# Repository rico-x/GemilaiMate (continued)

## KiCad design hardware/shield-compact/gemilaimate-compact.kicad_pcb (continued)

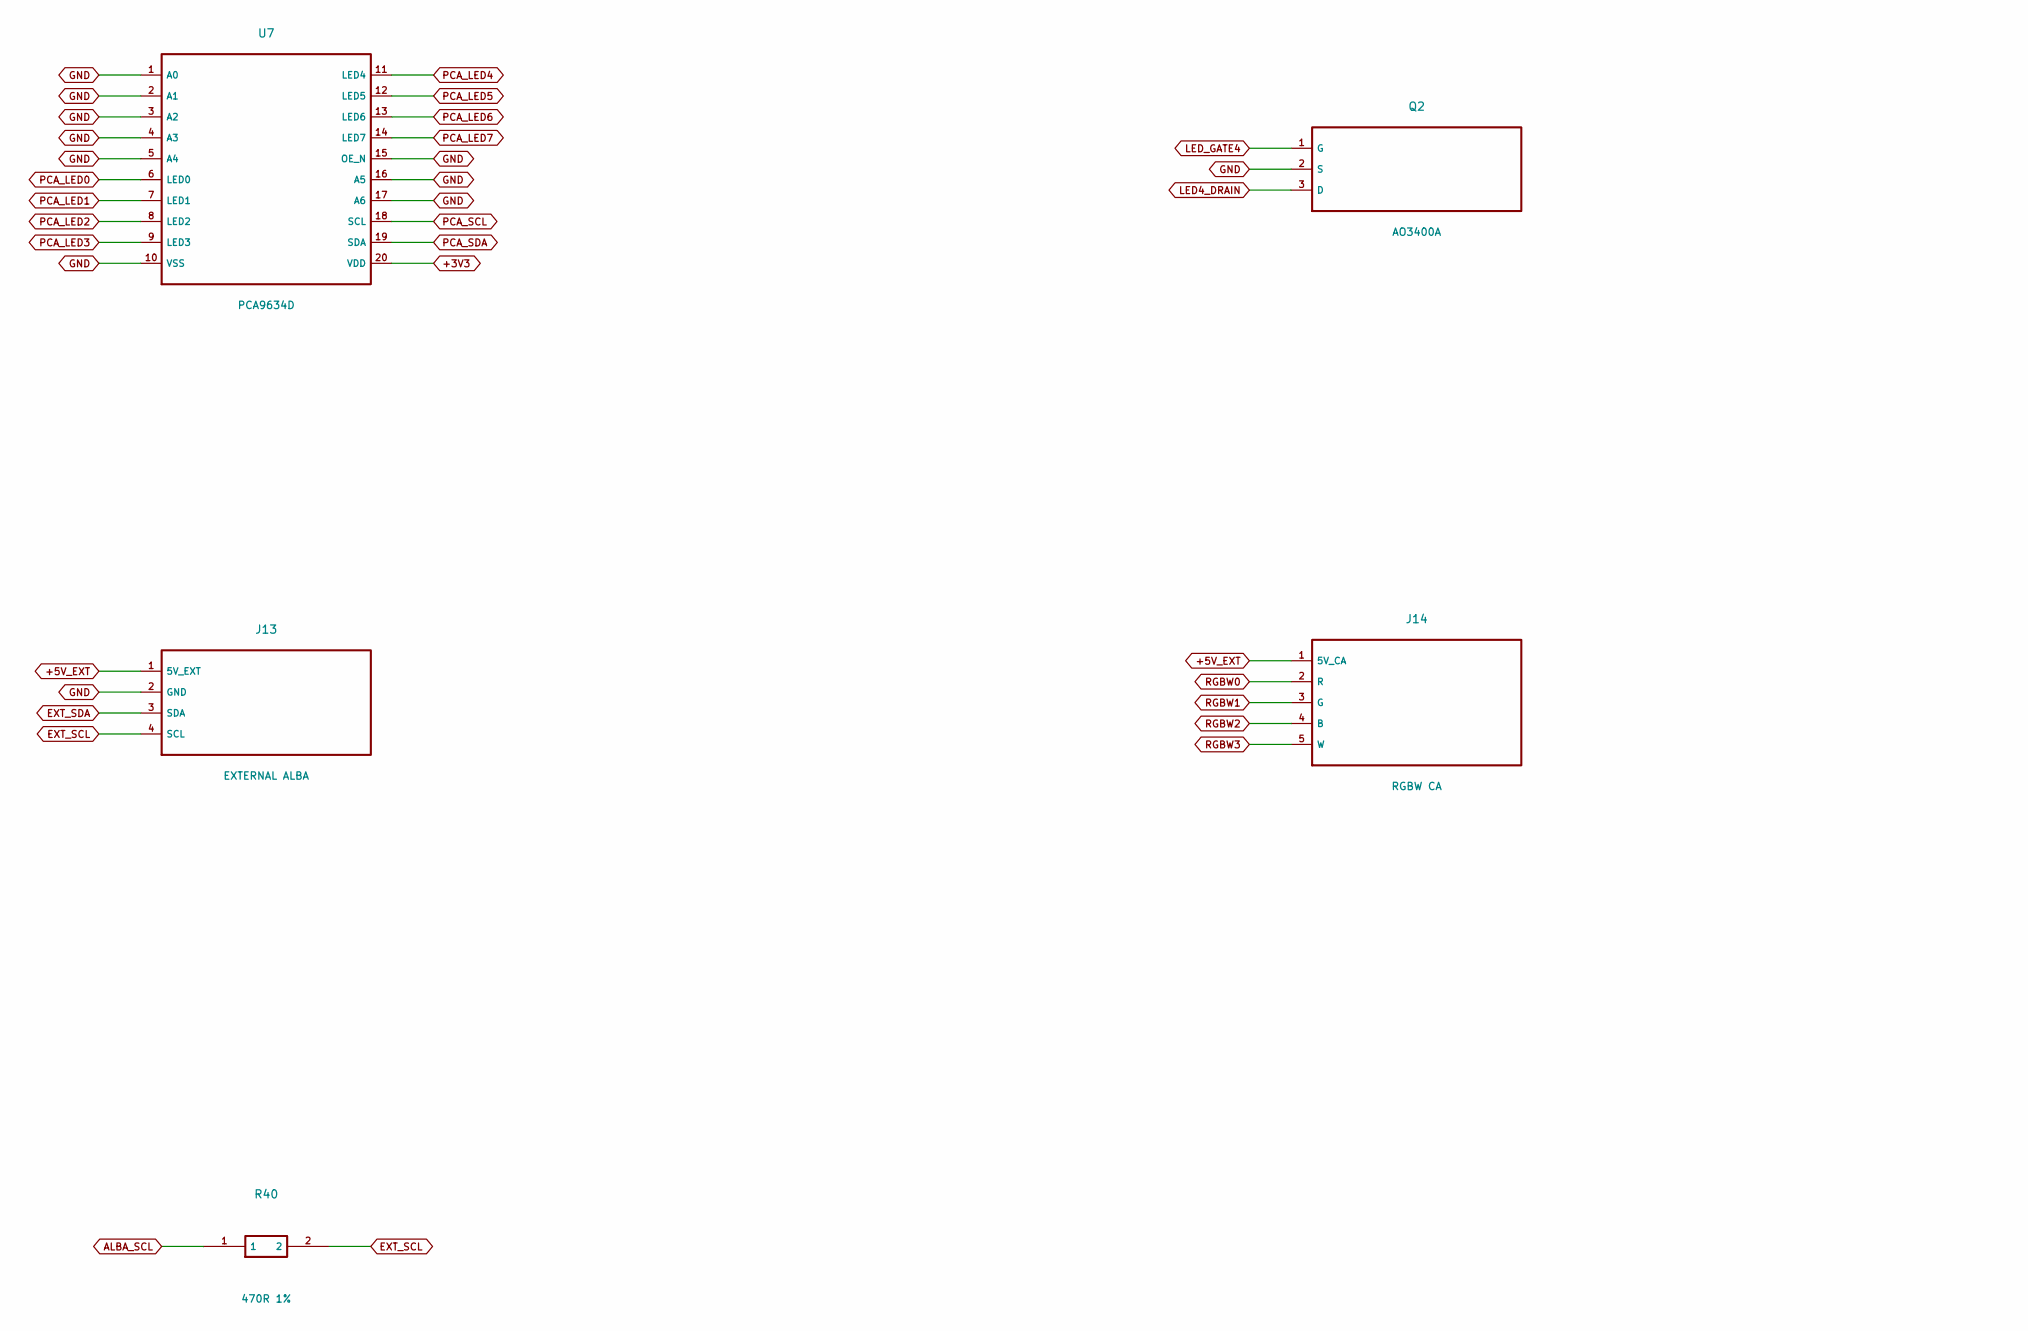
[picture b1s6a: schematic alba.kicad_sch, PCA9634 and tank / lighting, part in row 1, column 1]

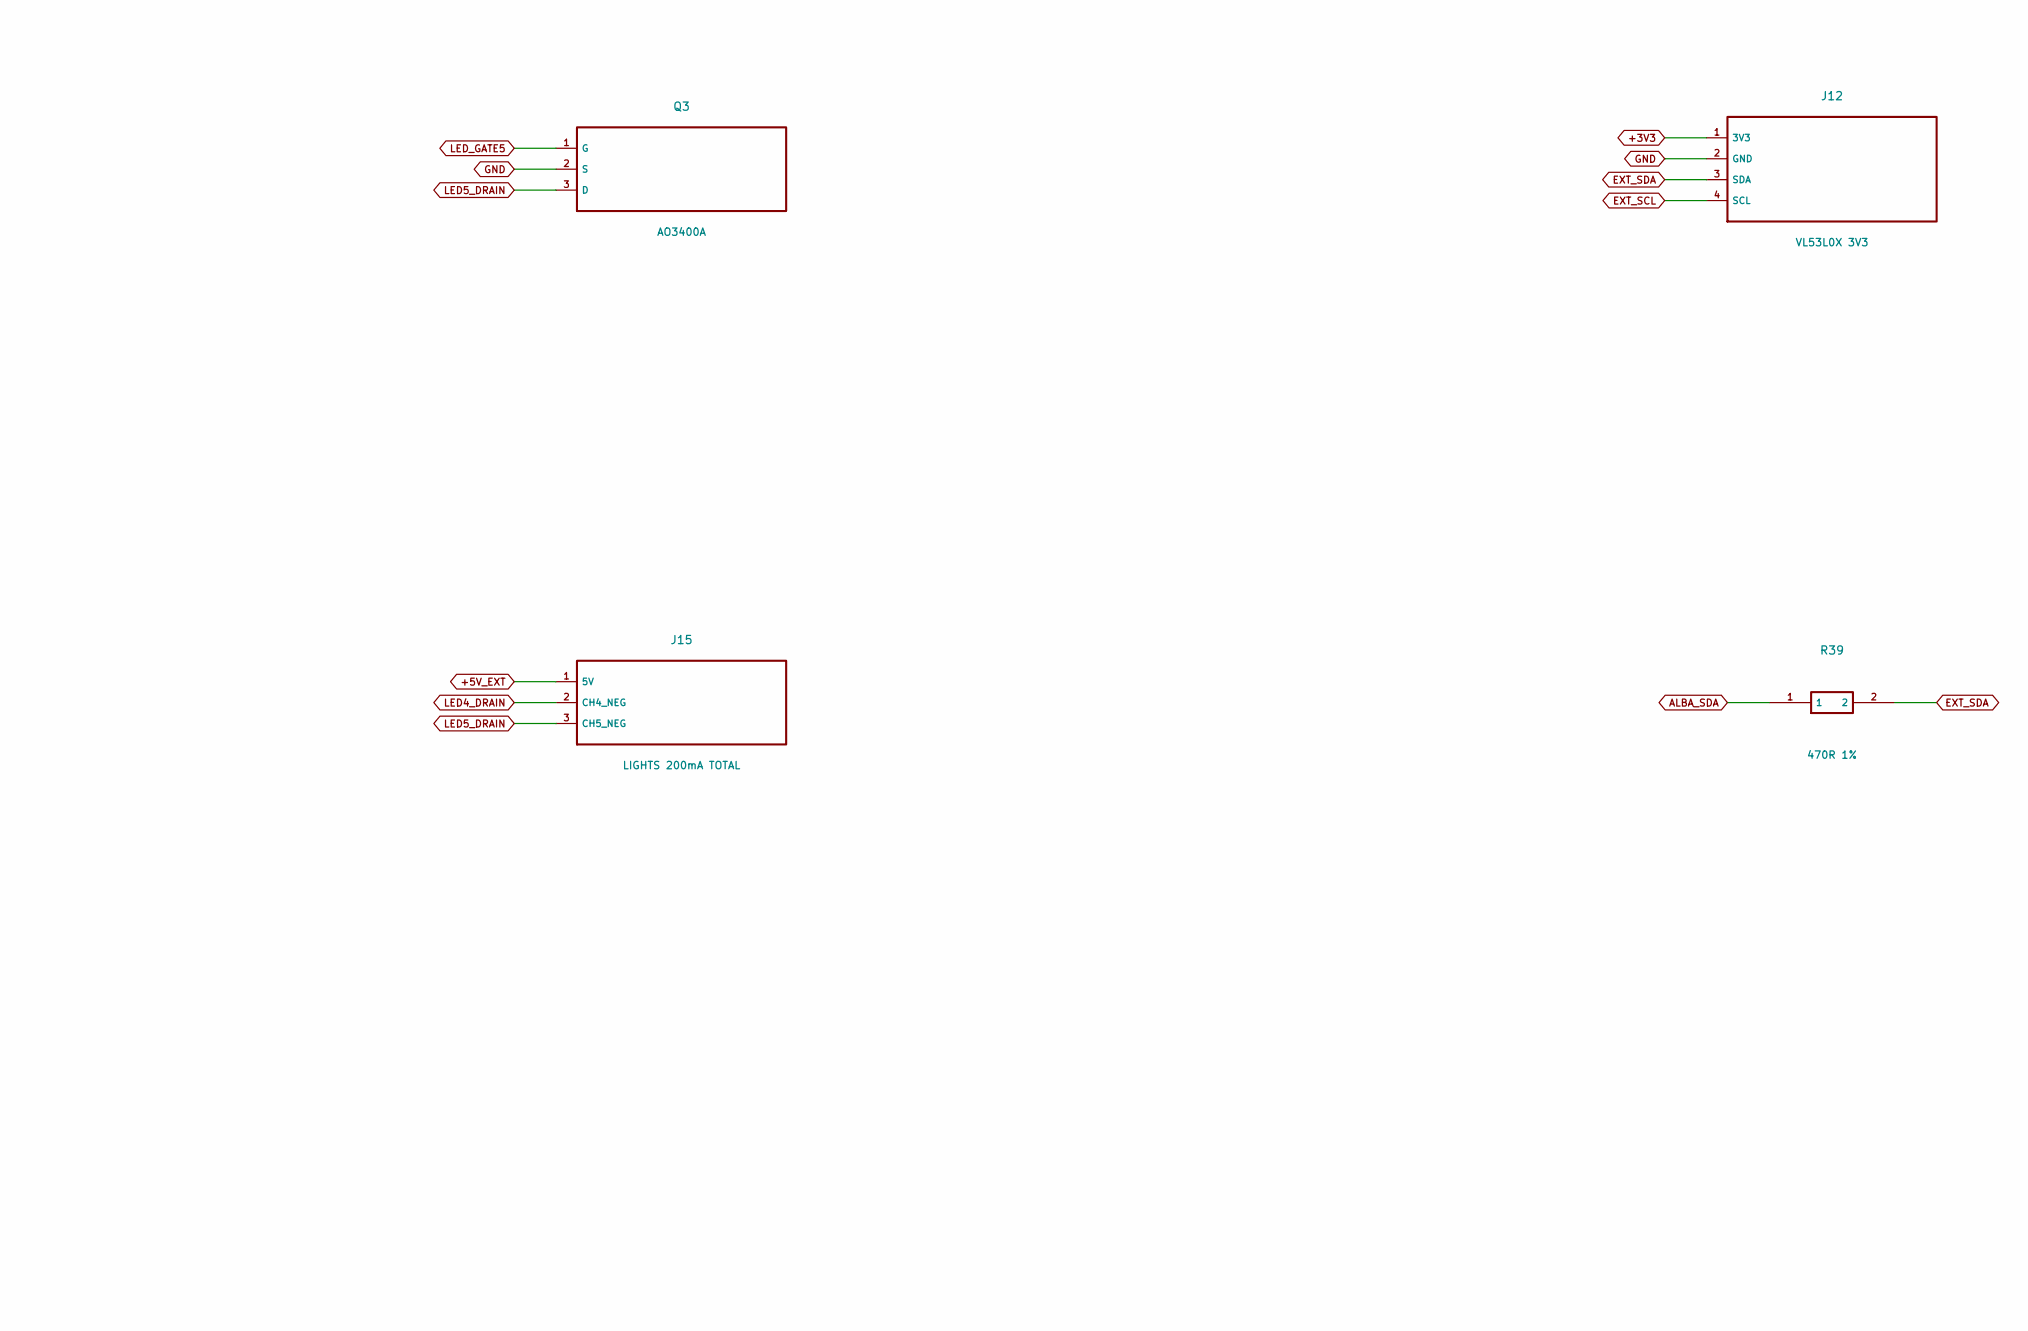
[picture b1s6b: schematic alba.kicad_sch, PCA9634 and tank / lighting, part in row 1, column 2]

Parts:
J12: VL53L0X 3V3; JST_PH_B4B-PH-K_1x04_P2.00mm_Vertical
J13: EXTERNAL ALBA; JST_PH_B4B-PH-K_1x04_P2.00mm_Vertical
J14: RGBW CA; JST_PH_B5B-PH-K_1x05_P2.00mm_Vertical
J15: LIGHTS 200mA TOTAL; JST_PH_B3B-PH-K_1x03_P2.00mm_Vertical
Q2, Q3: AO3400A; SOT-23_Handsoldering
R39, R40: 470R 1%; R_0805_2012Metric_Pad1.20x1.40mm_HandSolder
U7: PCA9634D; SOIC-20W_7.5x12.8mm_P1.27mm

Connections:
+3V3: J12.1 (3V3), U7.20 (VDD); also elsewhere on the board
+5V_EXT: J13.1 (5V_EXT), J14.1 (5V_CA), J15.1 (5V); also elsewhere on the board
ALBA_SCL: R40.1; also elsewhere on the board
ALBA_SDA: R39.1; also elsewhere on the board
EXT_SCL: J12.4 (SCL), J13.4 (SCL), R40.2
EXT_SDA: J12.3 (SDA), J13.3 (SDA), R39.2
GND: J12.2 (GND), J13.2 (GND), Q2.2 (S), Q3.2 (S), U7.1 (A0), U7.2 (A1), U7.3 (A2), U7.4 (A3), U7.5 (A4), U7.10 (VSS), U7.15 (OE_N), U7.16 (A5), U7.17 (A6); also elsewhere on the board
LED4_DRAIN: J15.2 (CH4_NEG), Q2.3 (D)
LED5_DRAIN: J15.3 (CH5_NEG), Q3.3 (D)
LED_GATE4: Q2.1 (G); also elsewhere on the board
LED_GATE5: Q3.1 (G); also elsewhere on the board
PCA_LED0: U7.6 (LED0); also elsewhere on the board
PCA_LED1: U7.7 (LED1); also elsewhere on the board
PCA_LED2: U7.8 (LED2); also elsewhere on the board
PCA_LED3: U7.9 (LED3); also elsewhere on the board
PCA_LED4: U7.11 (LED4); also elsewhere on the board
PCA_LED5: U7.12 (LED5); also elsewhere on the board
PCA_LED6: U7.13 (LED6); also elsewhere on the board
PCA_LED7: U7.14 (LED7); also elsewhere on the board
PCA_SCL: U7.18 (SCL); also elsewhere on the board
PCA_SDA: U7.19 (SDA); also elsewhere on the board
RGBW0: J14.2 (R); also elsewhere on the board
RGBW1: J14.3 (G); also elsewhere on the board
RGBW2: J14.4 (B); also elsewhere on the board
RGBW3: J14.5 (W); also elsewhere on the board

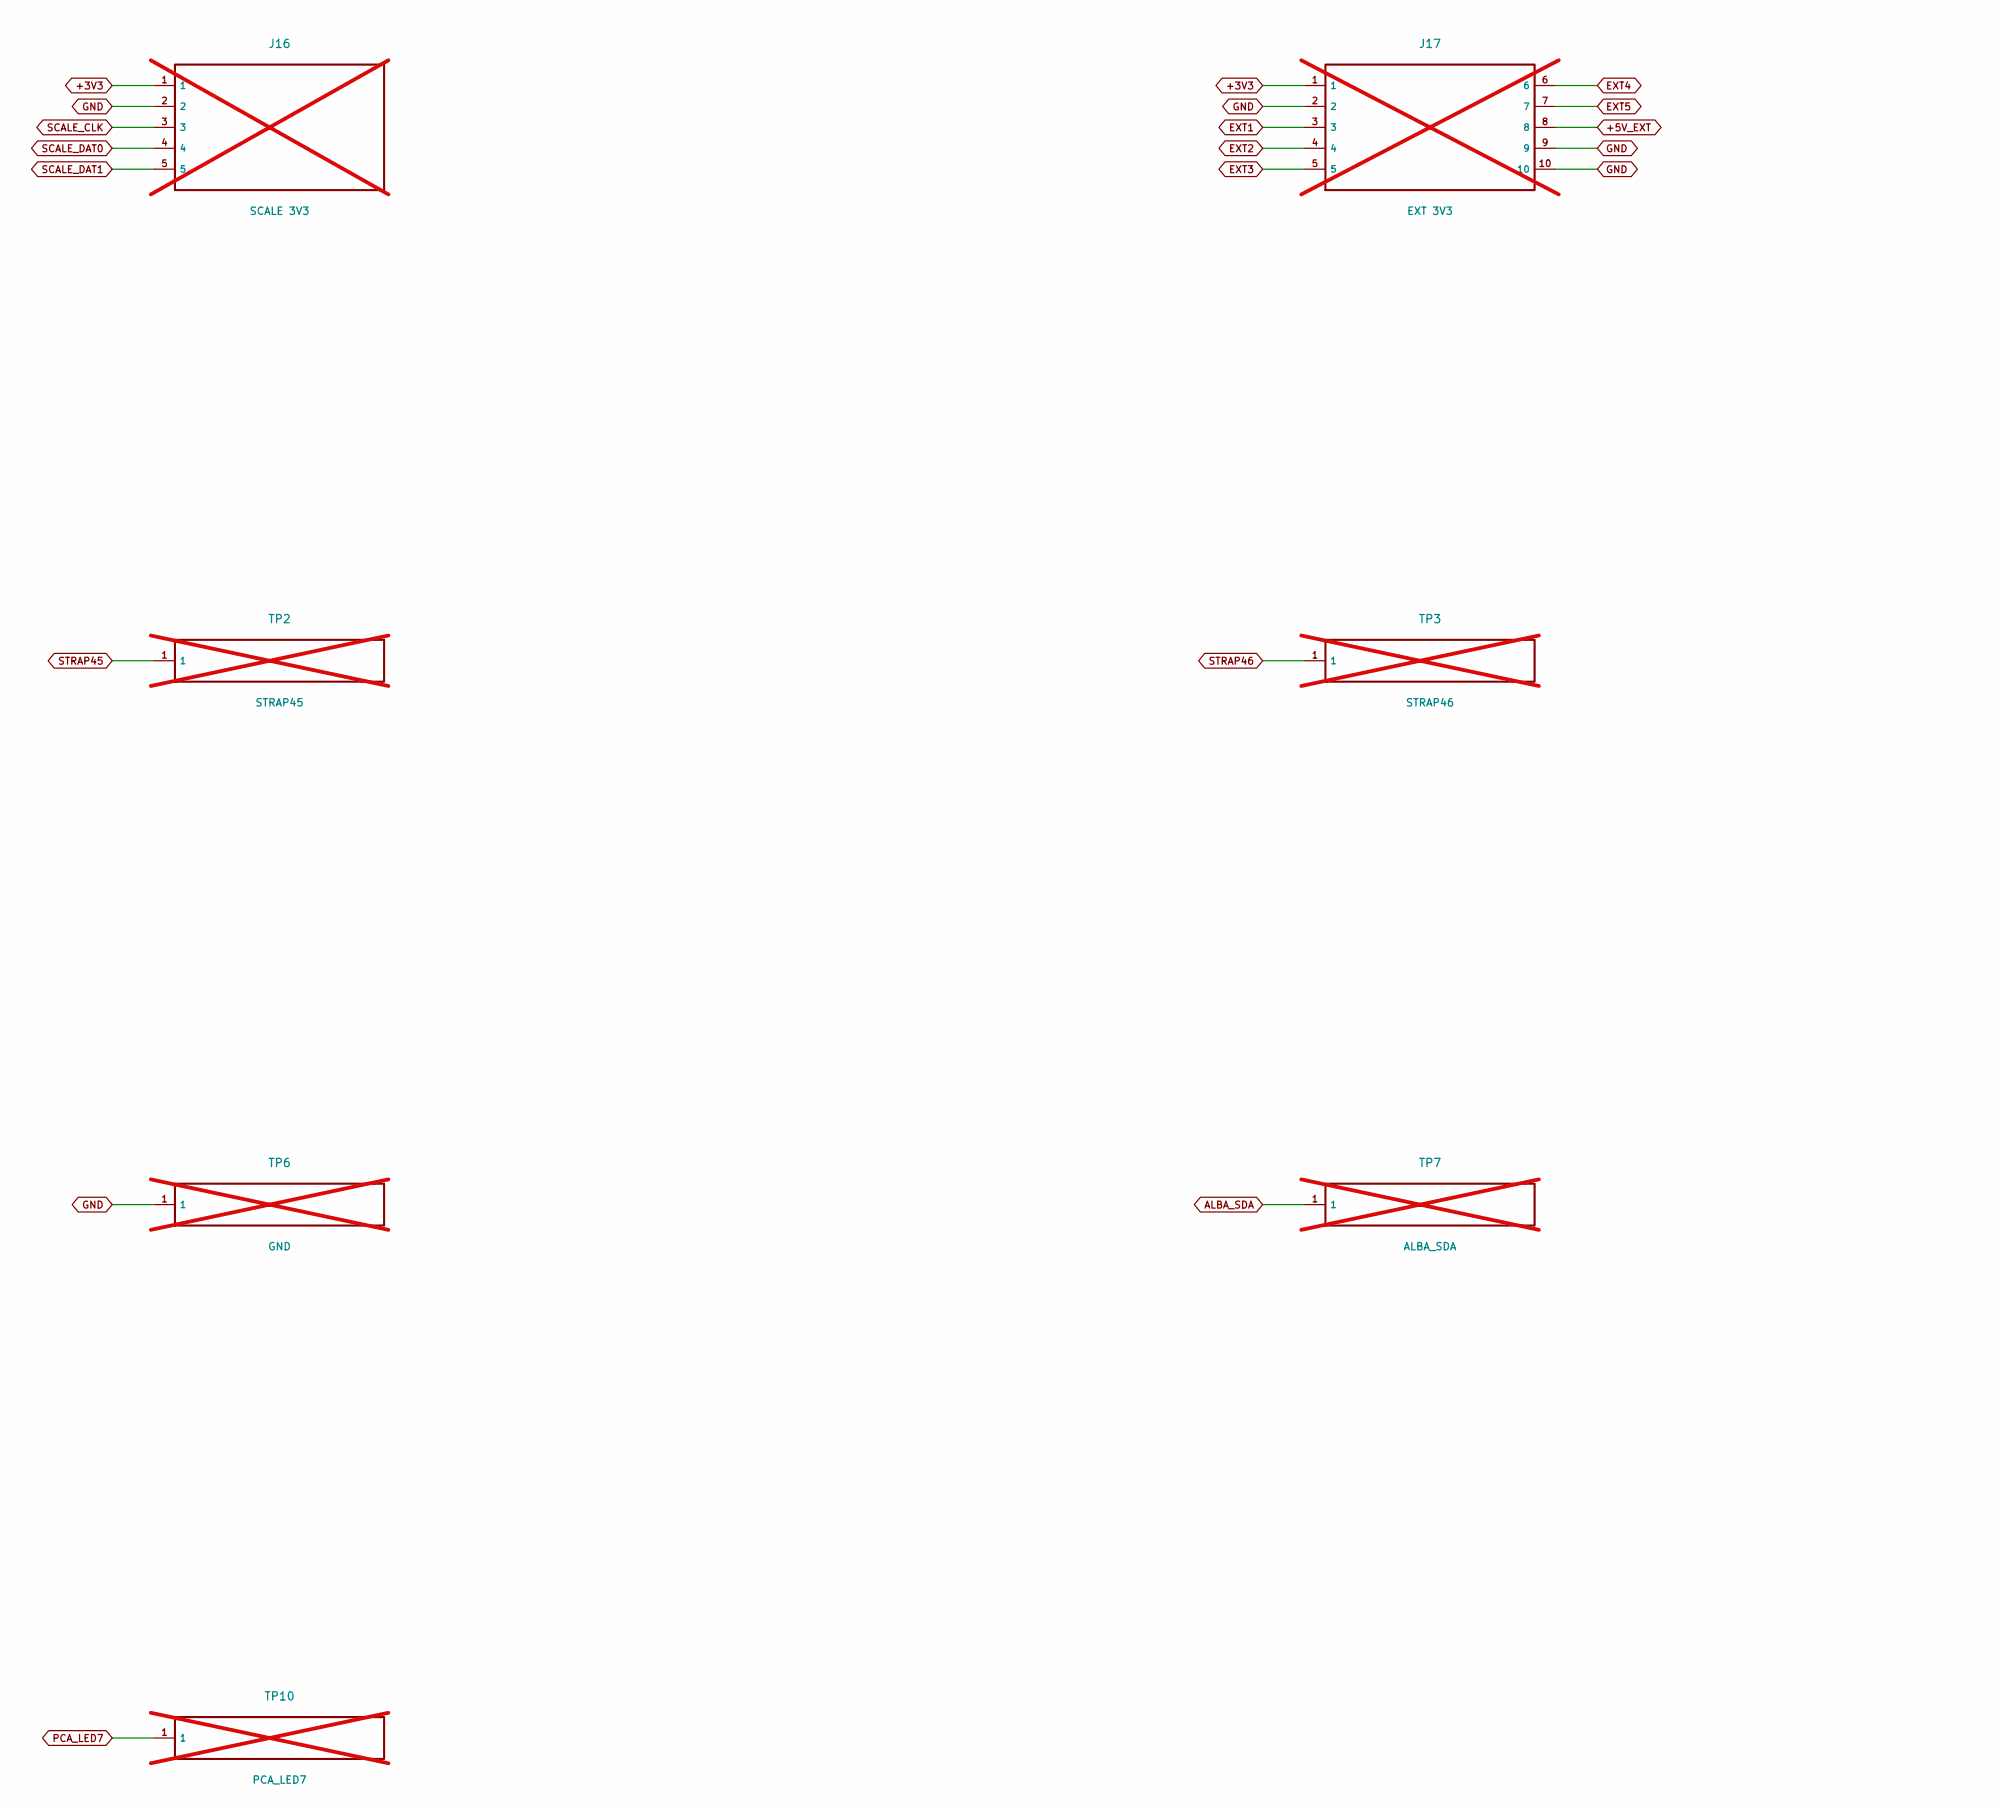
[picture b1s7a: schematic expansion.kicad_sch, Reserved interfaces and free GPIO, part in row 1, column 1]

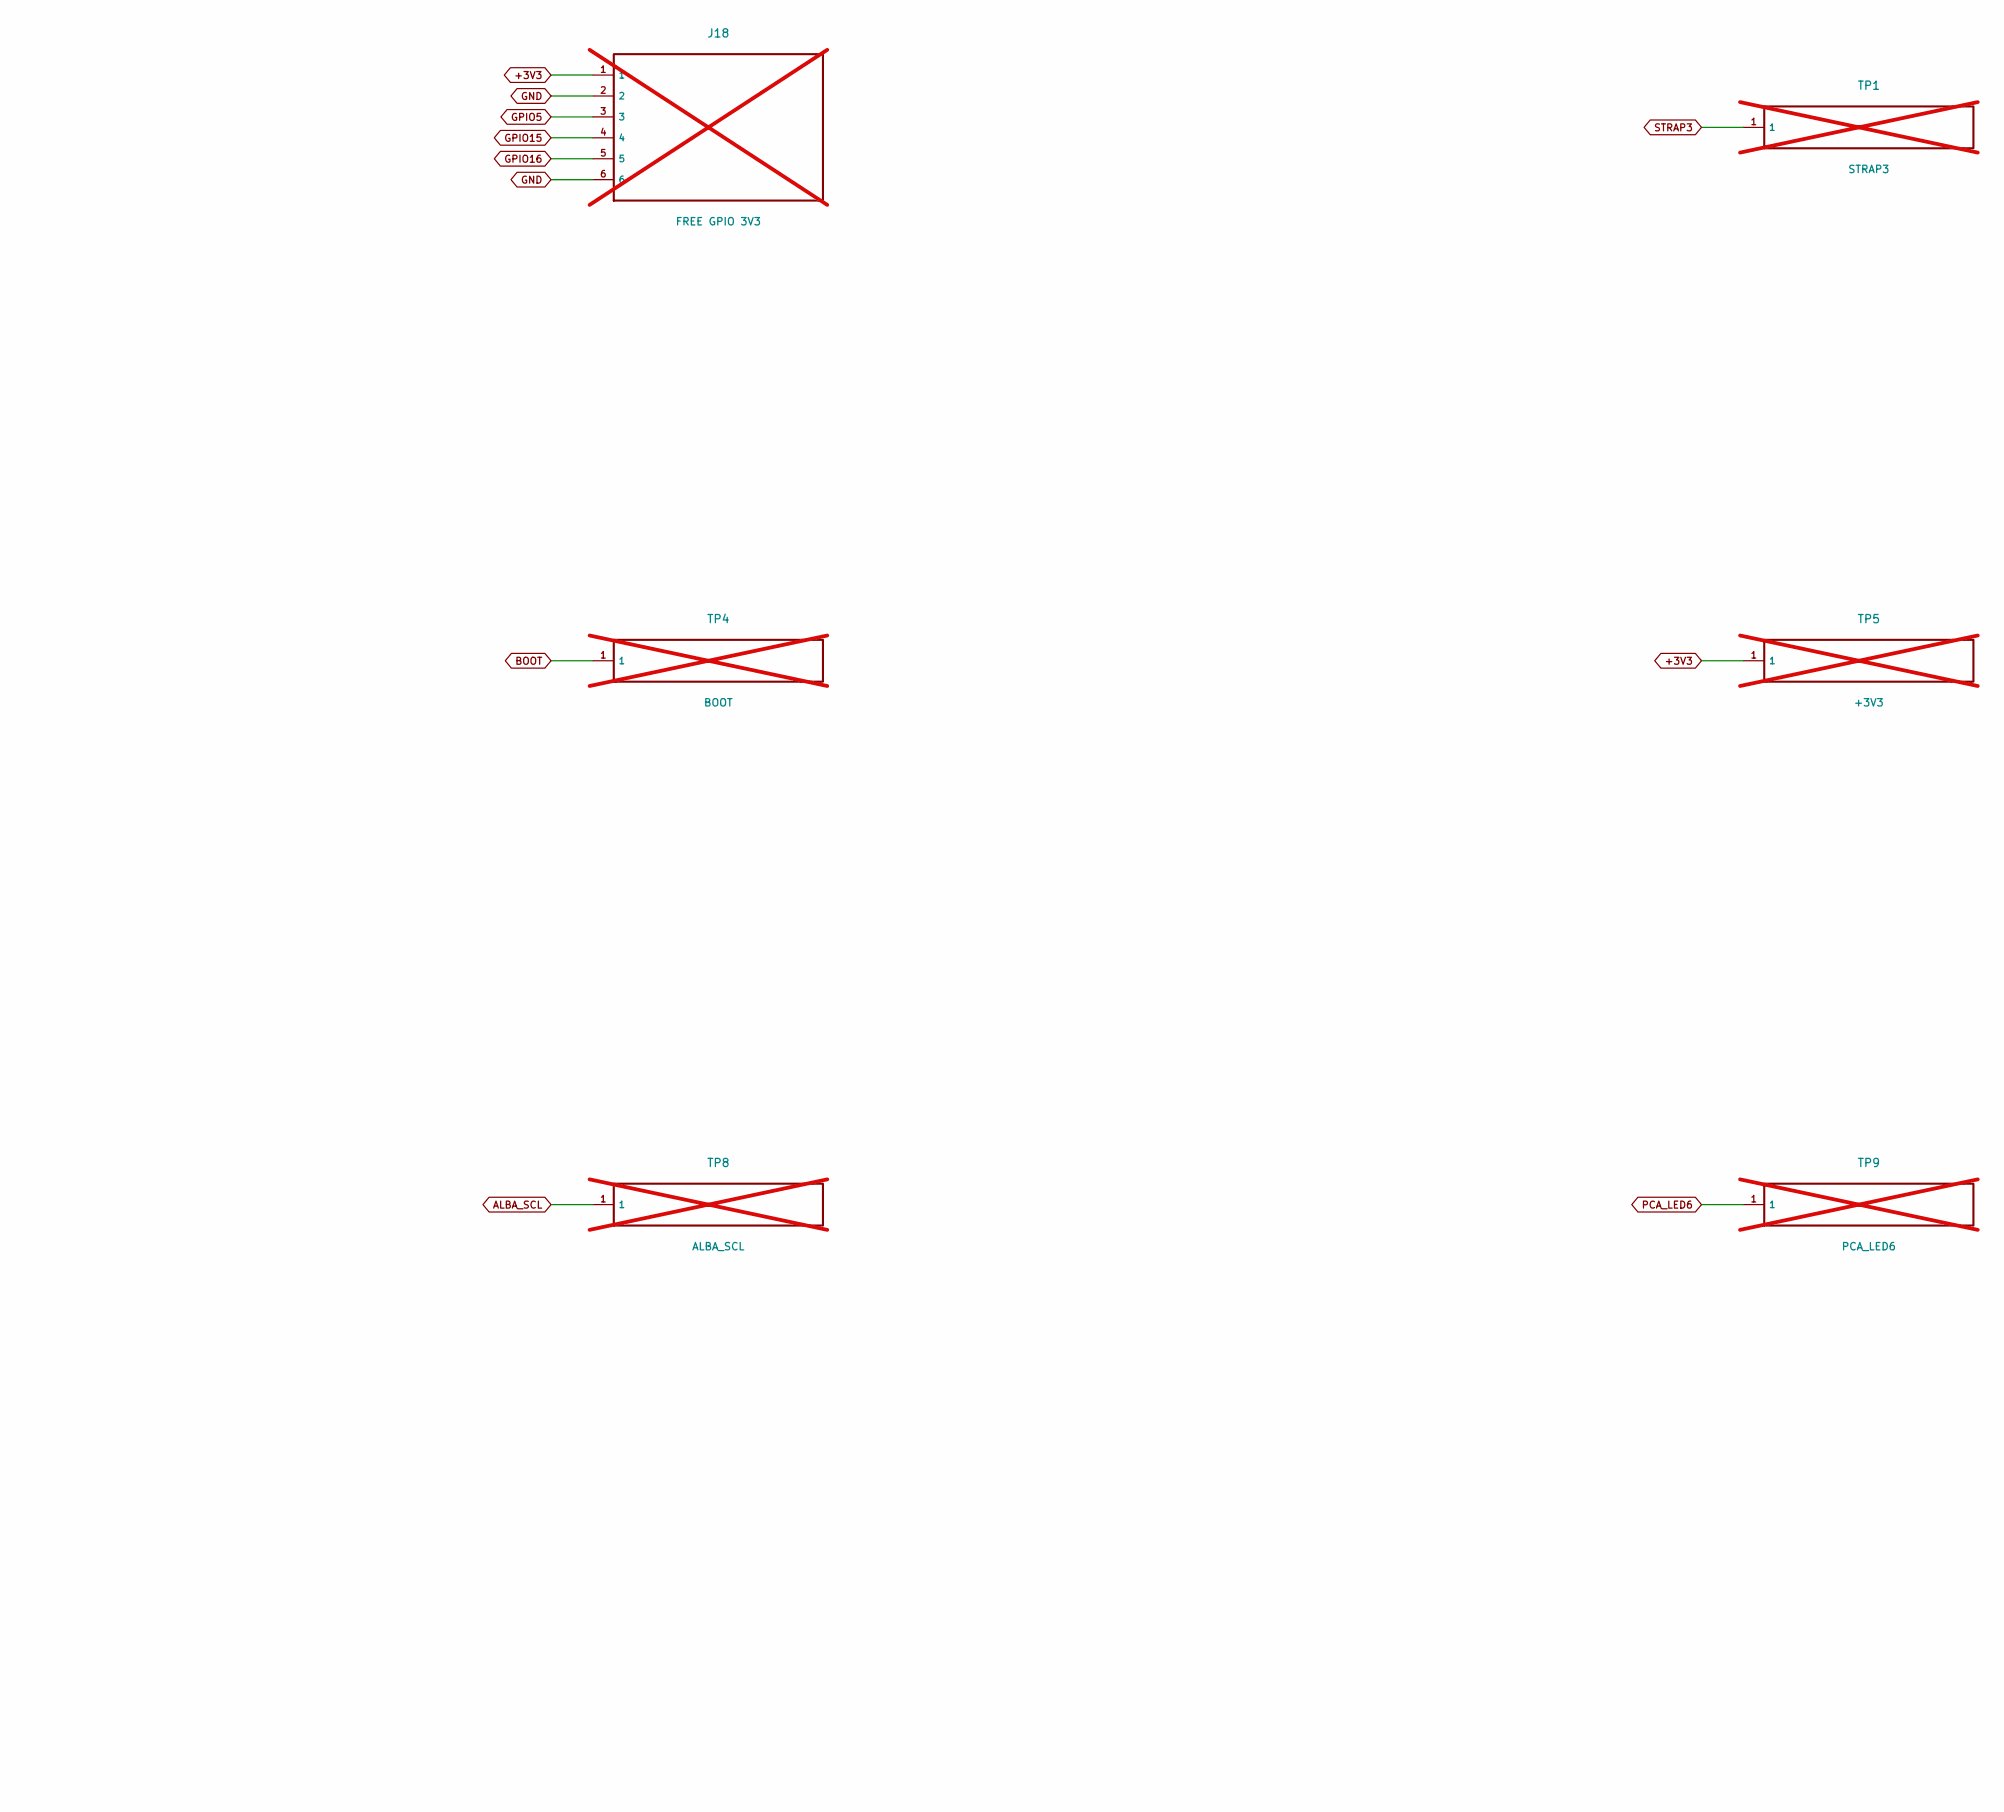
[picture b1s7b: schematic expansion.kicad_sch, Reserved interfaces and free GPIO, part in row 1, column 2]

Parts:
J16: SCALE 3V3; PinHeader_1x05_P2.54mm_Vertical; not fitted
J17: EXT 3V3; PinHeader_2x05_P2.54mm_Vertical; not fitted
J18: FREE GPIO 3V3; PinHeader_1x06_P2.54mm_Vertical; not fitted
TP1: STRAP3; TestPoint_Pad_D1.0mm; not fitted
TP2: STRAP45; TestPoint_Pad_D1.0mm; not fitted
TP3: STRAP46; TestPoint_Pad_D1.0mm; not fitted
TP4: BOOT; TestPoint_Pad_D1.0mm; not fitted
TP5: +3V3; TestPoint_Pad_D1.0mm; not fitted
TP6: GND; TestPoint_Pad_D1.0mm; not fitted
TP7: ALBA_SDA; TestPoint_Pad_D1.0mm; not fitted
TP8: ALBA_SCL; TestPoint_Pad_D1.0mm; not fitted
TP9: PCA_LED6; TestPoint_Pad_D1.0mm; not fitted
TP10: PCA_LED7; TestPoint_Pad_D1.0mm; not fitted

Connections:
+3V3: J16.1, J17.1, J18.1, TP5.1 (1_1); also elsewhere on the board
+5V_EXT: J17.8; also elsewhere on the board
ALBA_SCL: TP8.1 (1_1); also elsewhere on the board
ALBA_SDA: TP7.1 (1_1); also elsewhere on the board
BOOT: TP4.1 (1_1); also elsewhere on the board
EXT1: J17.3; also elsewhere on the board
EXT2: J17.4; also elsewhere on the board
EXT3: J17.5; also elsewhere on the board
EXT4: J17.6; also elsewhere on the board
EXT5: J17.7; also elsewhere on the board
GND: J16.2, J17.2, J17.9, J17.10, J18.2, J18.6, TP6.1 (1_1); also elsewhere on the board
GPIO5: J18.3; also elsewhere on the board
GPIO15: J18.4; also elsewhere on the board
GPIO16: J18.5; also elsewhere on the board
PCA_LED6: TP9.1 (1_1); also elsewhere on the board
PCA_LED7: TP10.1 (1_1); also elsewhere on the board
SCALE_CLK: J16.3; also elsewhere on the board
SCALE_DAT0: J16.4; also elsewhere on the board
SCALE_DAT1: J16.5; also elsewhere on the board
STRAP3: TP1.1 (1_1); also elsewhere on the board
STRAP45: TP2.1 (1_1); also elsewhere on the board
STRAP46: TP3.1 (1_1); also elsewhere on the board

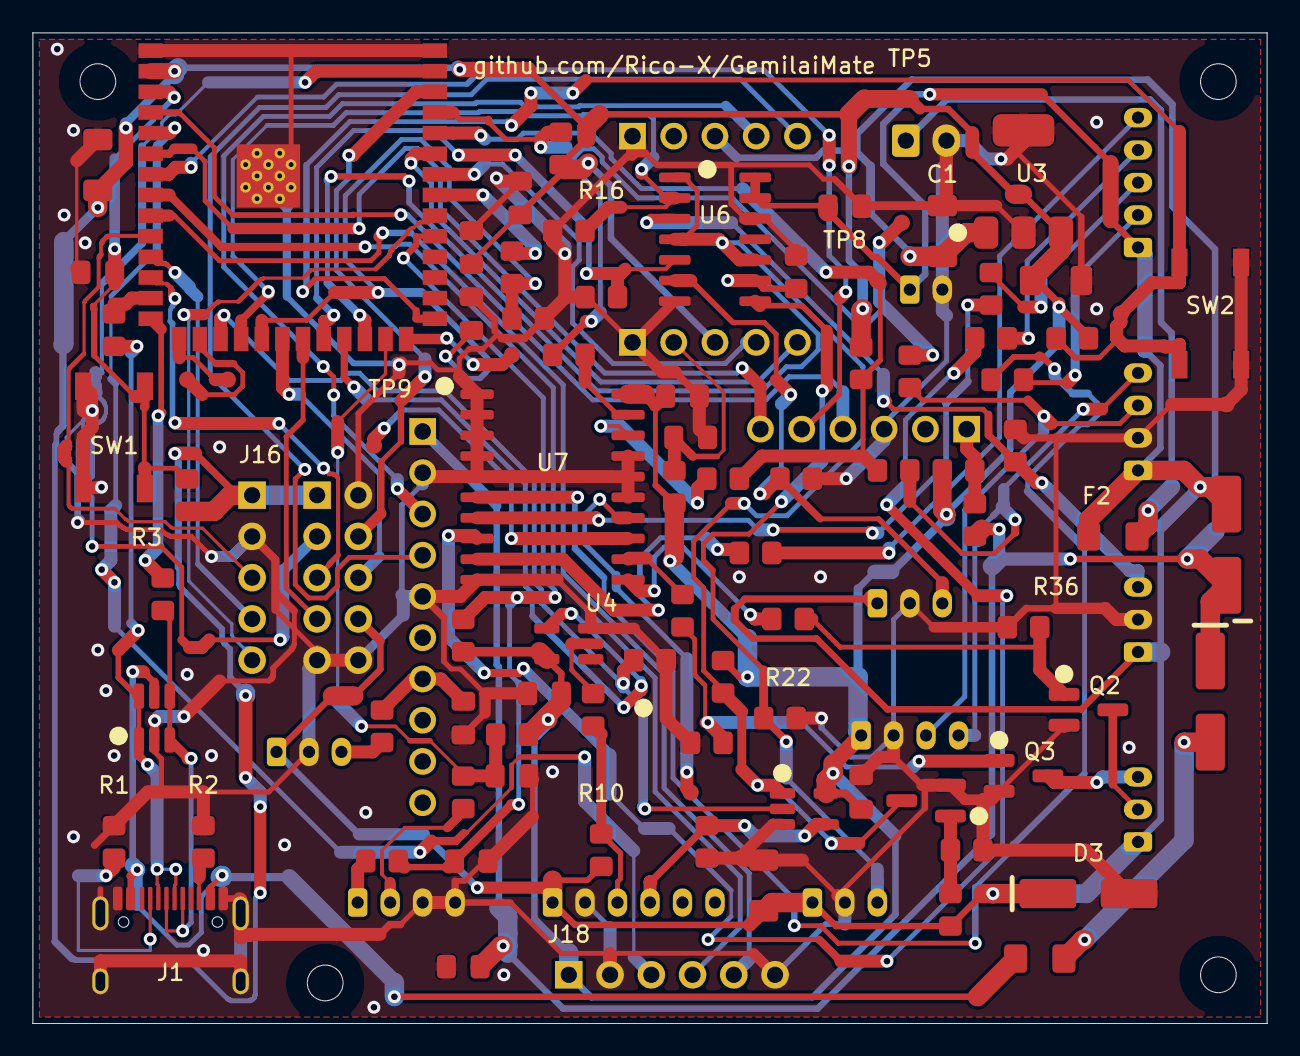
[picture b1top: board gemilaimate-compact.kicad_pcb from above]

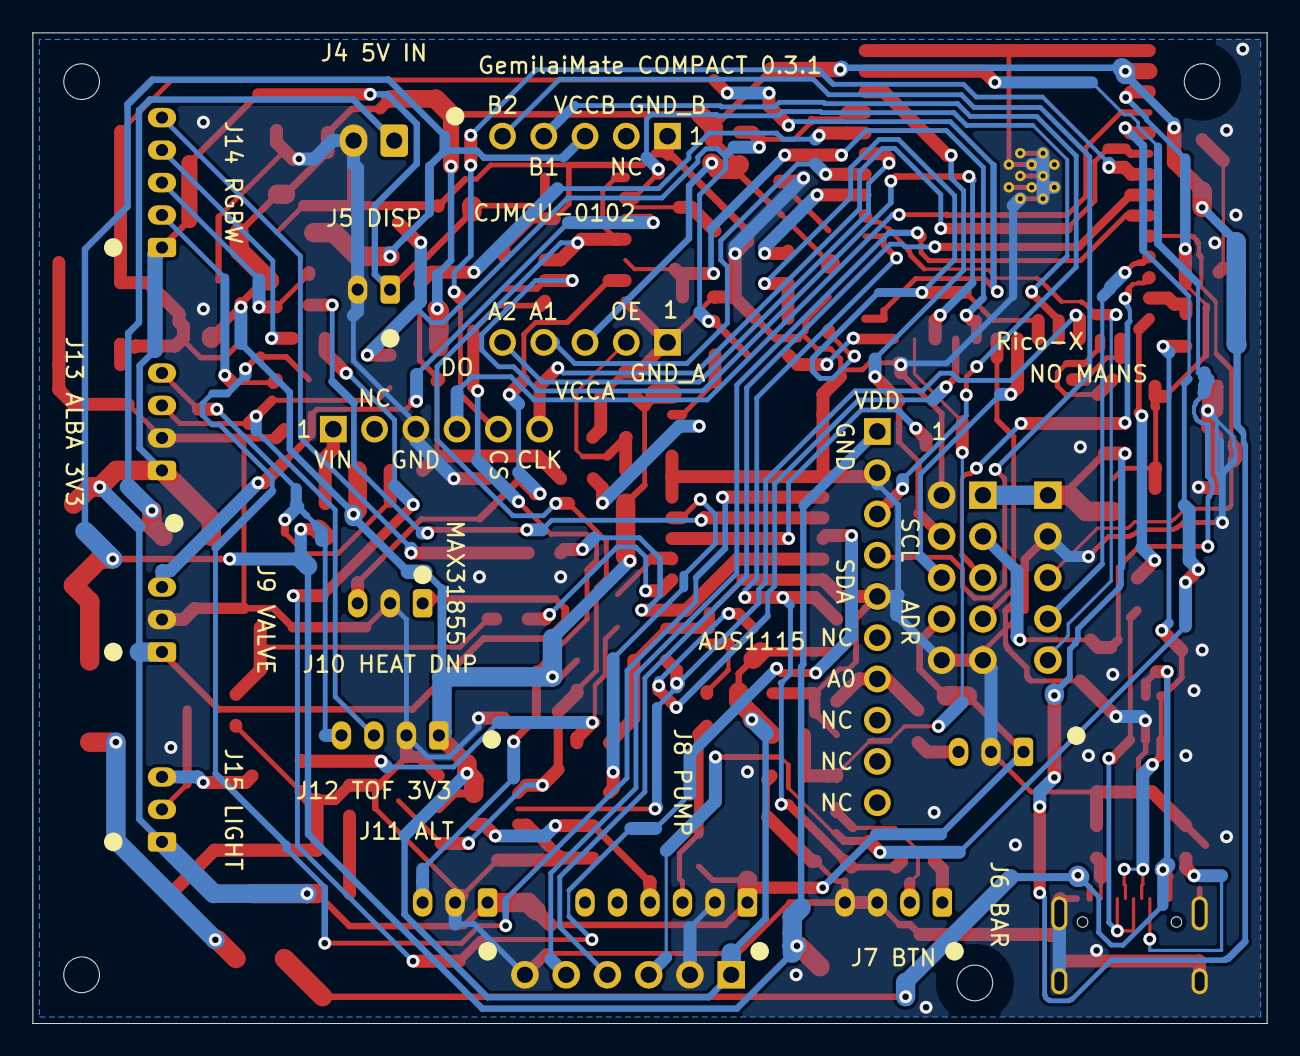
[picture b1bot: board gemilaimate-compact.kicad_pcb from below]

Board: 2 copper layers, 76.0 x 61.0 mm, 110 parts (12 on the bottom side), 81 nets.

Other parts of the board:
H1, H2, H3, H4: M2 NYLON

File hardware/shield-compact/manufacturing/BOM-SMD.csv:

Designators,Quantity_1_PCB,Quantity_5_PCB,Value,MPN_example,Footprint
U1,1,5,ESP32-S3-WROOM-1-N16R8,ESP32-S3-WROOM-1-N16R8,GemilaiMateCompact:ESP32-S3-WROOM-1
J1,1,5,TYPE-C-31-M-12,TYPE-C-31-M-12,GemilaiMateCompact:USB_C_Receptacle_HRO_TYPE-C-31-M-12
R1 R2,2,10,5.1k 1%,RC0805FR-075K1L,GemilaiMateCompact:R_0805_2012Metric_Pad1.20x1.40mm_HandSolder
R3 R4,2,10,22R 1%,RC0805FR-0722RL,GemilaiMateCompact:R_0805_2012Metric_Pad1.20x1.40mm_HandSolder
U2,1,5,USBLC6-2SC6,USBLC6-2SC6,GemilaiMateCompact:SOT-23-6_Handsoldering
F1,1,5,1206L050YR 0.5A,1206L050YR,GemilaiMateCompact:Fuse_1206_3216Metric_Pad1.42x1.75mm_HandSolder
F2,1,5,1206L150/12 1.5A,1206L150/12SLYR,GemilaiMateCompact:Fuse_1206_3216Metric_Pad1.42x1.75mm_HandSolder
D1 D2,2,10,SS14,SS14-13-F,GemilaiMateCompact:D_SMA_Handsoldering
U3,1,5,AP7361C-33E-13,AP7361C-33E-13,GemilaiMateCompact:SOT-223-3_TabPin2
C1 C2 C3 C16,4,20,10uF 16V X7R,GRM31CR71C106KAC7L,GemilaiMateCompact:C_1206_3216Metric_Pad1.33x1.80mm_HandSolder
C4 C7 C8 C9 C10 C11 C12 C13 C14 C15,10,50,100nF 50V X7R,GRM21BR71H104KA01L,GemilaiMateCompact:C_0805_2012Metric_Pad1.18x1.45mm_HandSolder
R5 R6 R7 R10 R14 R15 R16 R17 R18 R19 R20 R21 R22 R24 R26 R43,16,80,10k 1%,RC0805FR-0710KL,GemilaiMateCompact:R_0805_2012Metric_Pad1.20x1.40mm_HandSolder
C5 C17,2,10,1uF 16V X7R,GRM21BR71C105KA01L,GemilaiMateCompact:C_0805_2012Metric_Pad1.18x1.45mm_HandSolder
SW1,1,5,RESET,TL3342F160QG,GemilaiMateCompact:SW_SPST_TL3342
SW2,1,5,BOOT,TL3342F160QG,GemilaiMateCompact:SW_SPST_TL3342
R8,1,5,1.58k 1%,RC0805FR-071K58L,GemilaiMateCompact:R_0805_2012Metric_Pad1.20x1.40mm_HandSolder
C6,1,5,10nF 50V C0G,GRM2165C1H103JA01D,GemilaiMateCompact:C_0805_2012Metric_Pad1.18x1.45mm_HandSolder
R9 R11 R23 R25,4,20,1k 1%,RC0805FR-071KL,GemilaiMateCompact:R_0805_2012Metric_Pad1.20x1.40mm_HandSolder
U4,1,5,SN74LVC1G17DBVR,SN74LVC1G17DBVR,GemilaiMateCompact:SOT-23-5_HandSoldering
R12,1,5,47k 1%,RC0805FR-0747KL,GemilaiMateCompact:R_0805_2012Metric_Pad1.20x1.40mm_HandSolder
R13 R36 R38,3,15,100k 1%,RC0805FR-07100KL,GemilaiMateCompact:R_0805_2012Metric_Pad1.20x1.40mm_HandSolder
Q1,1,5,MMBT3904,MMBT3904-7-F,GemilaiMateCompact:SOT-23_Handsoldering
U5,1,5,SN74LVC1G125DBVR,SN74LVC1G125DBVR,GemilaiMateCompact:SOT-23-5_HandSoldering
U6,1,5,SN74AHCT125DR,SN74AHCT125DR,GemilaiMateCompact:SOIC-14_3.9x8.7mm_P1.27mm
U7,1,5,PCA9634D,"PCA9634D,118",GemilaiMateCompact:SOIC-20W_7.5x12.8mm_P1.27mm
R27 R28 R41,3,15,0R,RC0805JR-070RL,GemilaiMateCompact:R_0805_2012Metric_Pad1.20x1.40mm_HandSolder
R29 R30,2,10,4.7k 1%,RC0805FR-074K7L,GemilaiMateCompact:R_0805_2012Metric_Pad1.20x1.40mm_HandSolder
R31 R32 R33 R34,4,20,180R 1%,RC0805FR-07180RL,GemilaiMateCompact:R_0805_2012Metric_Pad1.20x1.40mm_HandSolder
R35 R37,2,10,100R 1%,RC0805FR-07100RL,GemilaiMateCompact:R_0805_2012Metric_Pad1.20x1.40mm_HandSolder
Q2 Q3,2,10,AO3400A,AO3400A,GemilaiMateCompact:SOT-23_Handsoldering
D3,1,5,SMAJ5.0A,SMAJ5.0A,GemilaiMateCompact:D_SMA_Handsoldering
R39 R40,2,10,470R 1%,RC0805FR-07470RL,GemilaiMateCompact:R_0805_2012Metric_Pad1.20x1.40mm_HandSolder
